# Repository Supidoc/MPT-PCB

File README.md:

# M.P.T.-PCB
The Multipurpose tracker (or just MPT) is a pocket sized device to track you habits. Although it is primarily designed to serve as a habit tracker it can be used for many other things. 

The MPT features a 2.79" 142x428 full color display. To control the device a 4-Way Joystick as well as 5 User Buttons are available.
At the core of the MPT sits an ESP32-S3. The ESP32-S3 has enough power to run the display at 30Hz, features WIFI and Bluetooth LE.
To get accurate timestamps for your habit entries a Microcrystal RTC module is included. The RTC is directly connected to the batteries so that it runs even when the rest of the system is in shutdown.
The whole system is powered by two 10440 570mAH LI-ION batteries by Keepower. The batteries already integrate a protection circuit. MPT features a fuel gauge and a charger to measure battery capacity and charge the device over USB-C. The USB-C Port also serves as the debug interface for ESP's JTAG-Over USB feature.

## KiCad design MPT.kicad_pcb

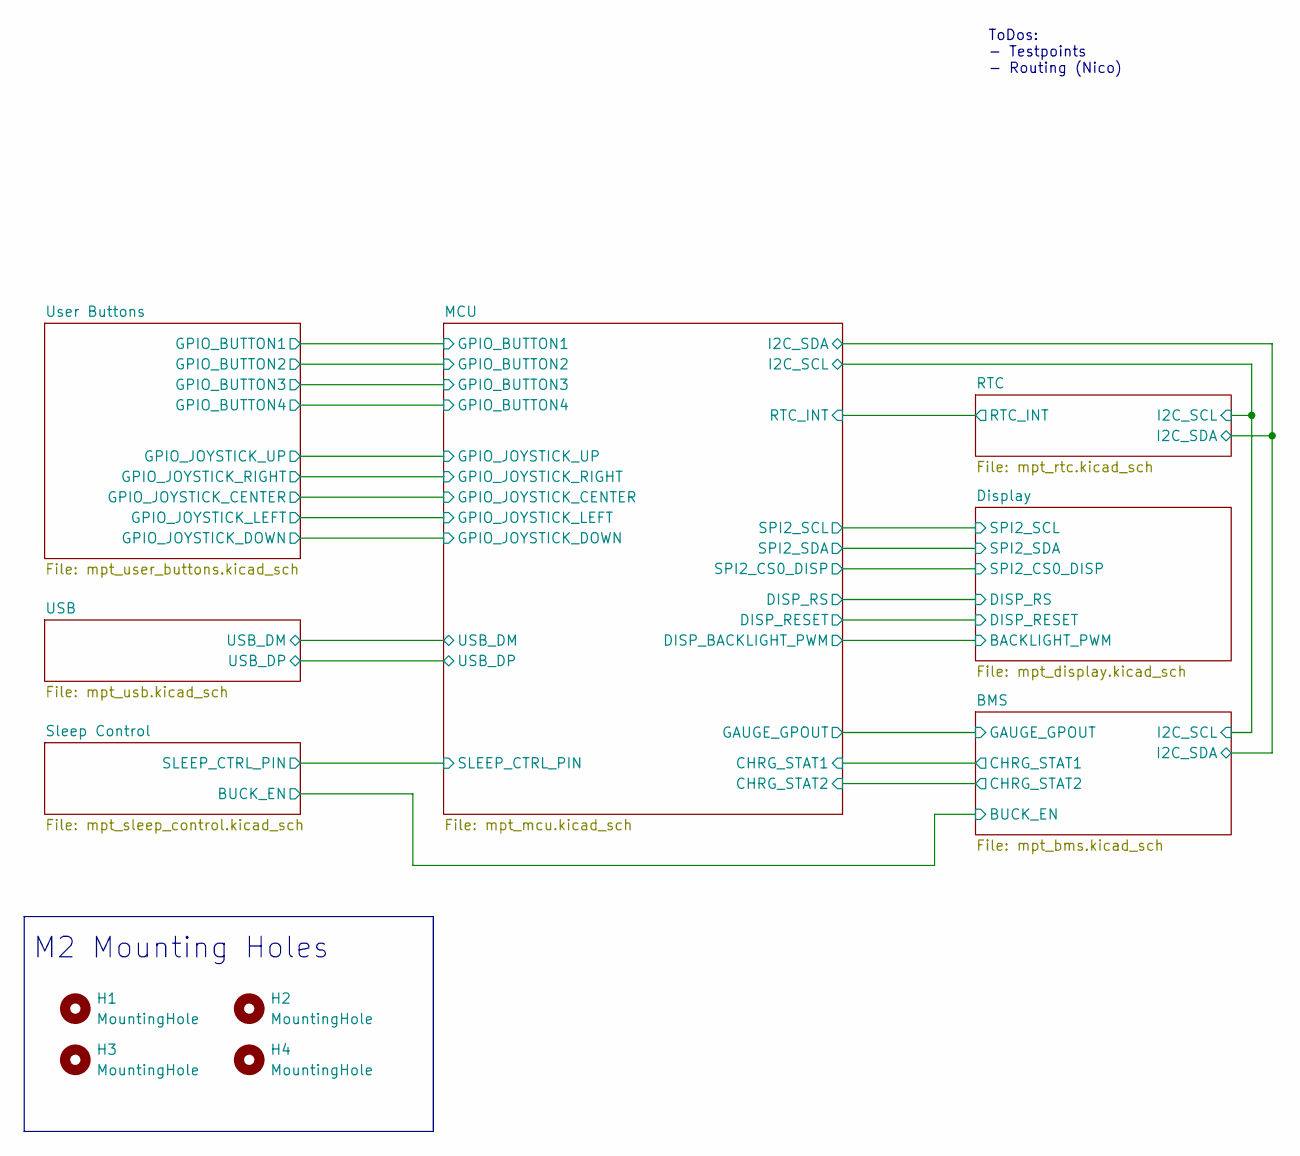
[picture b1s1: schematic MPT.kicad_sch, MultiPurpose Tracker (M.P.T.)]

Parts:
H1, H2, H3, H4: MountingHole; MountingHole_2.2mm_M2

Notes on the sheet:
ToDos: - Testpoints - Routing (Nico)
M2 Mounting Holes

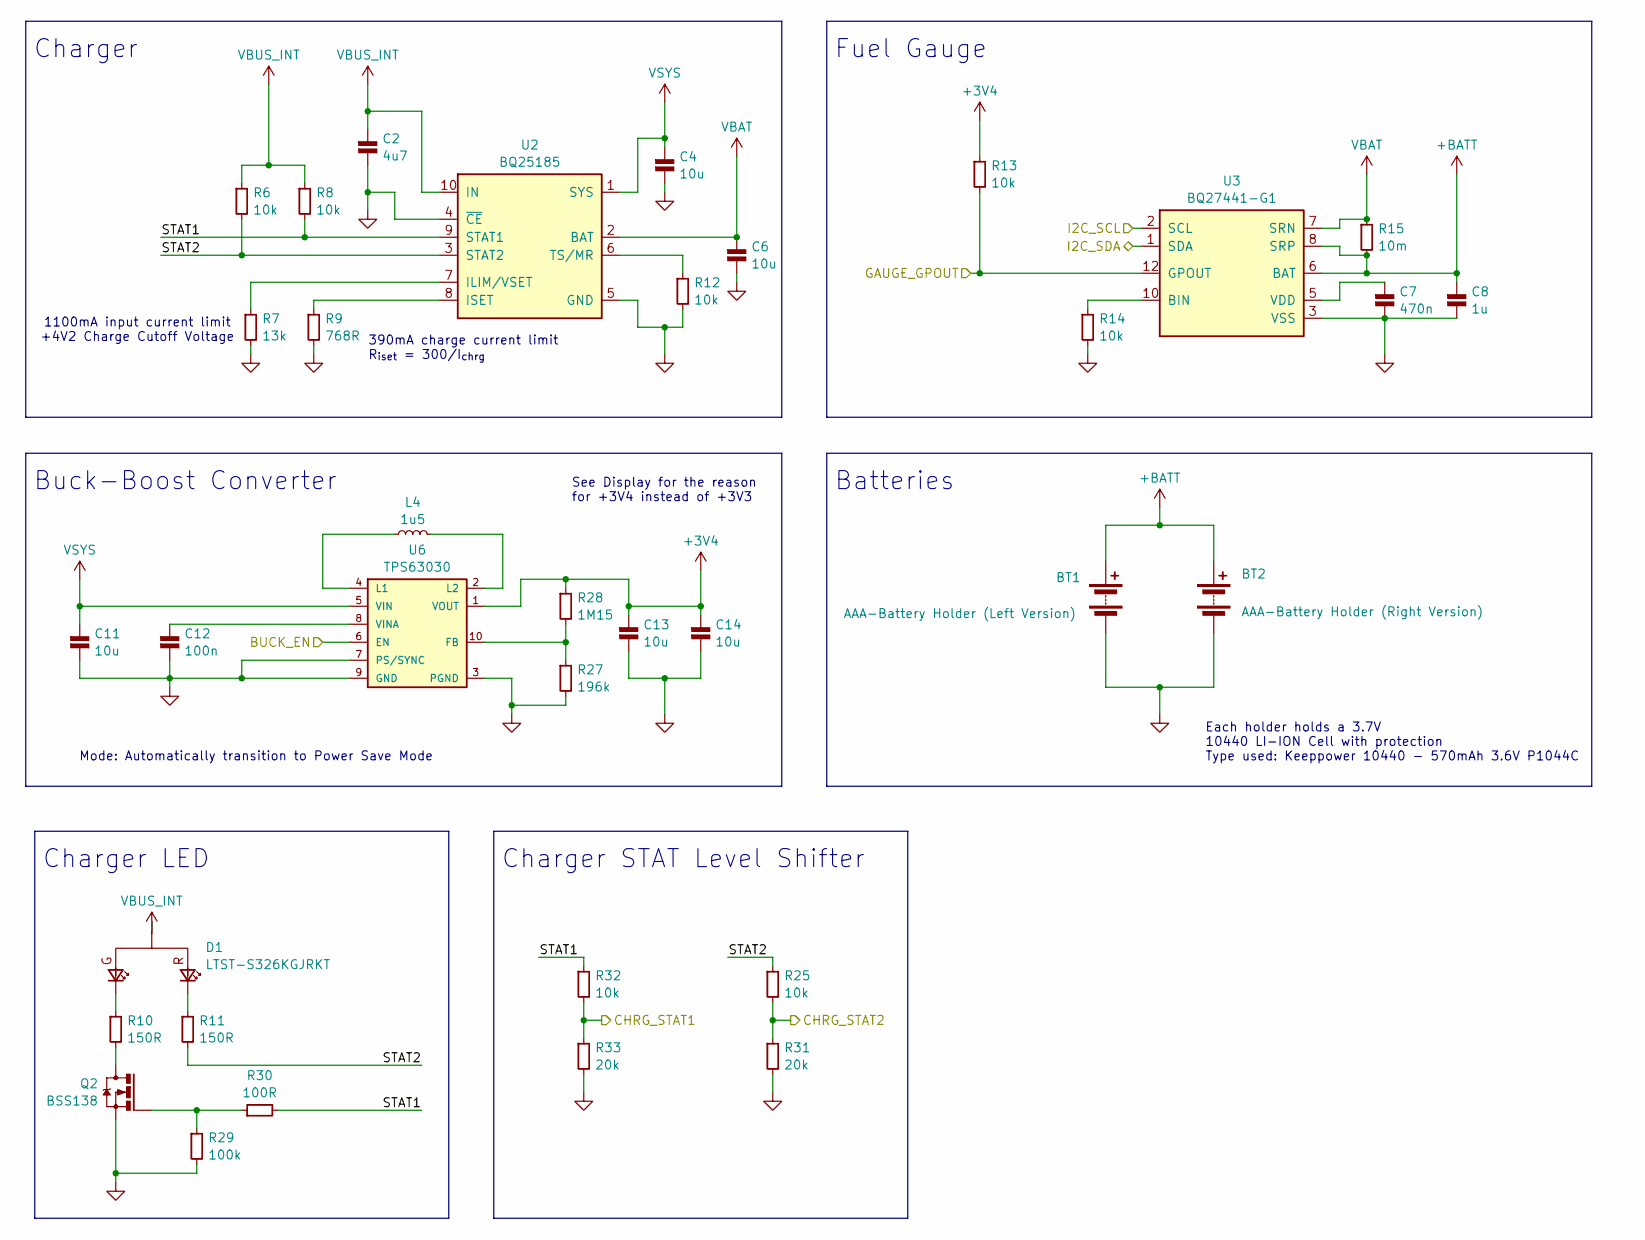
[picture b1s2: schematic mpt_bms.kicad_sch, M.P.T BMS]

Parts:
BT1: AAA-Battery Holder (Left Version); battery_holder_aaa_right_angle_left; MFR# 2466
BT2: AAA-Battery Holder (Right Version); battery_holder_aaa_right_angle_right; MFR# 2466
C2: 4u7; C_0805; Rating 25V 10%; MFR# CC0805KKX7R8BB475
C4, C6, C11, C13, C14: 10u; C_0603; Rating 10V 20%; MFR# CC0603MRX5R6BB106
C7: 470n; C_0603; Rating 16V 10%; MFR# CC0603KRX7R7BB474
C8: 1u; C_0603; Rating 50V 10%; MFR# CC0603KRX7R9BB105
C12: 100n; C_0603; Rating 25V 10%; MFR# CC0603KRX7R8BB104
D1: LTST-S326KGJRKT; LED_RG_0805_Right_Angle; Rating Red 2Vf, Green 2Vf; MFR# LTST-S326KGJRKT
L4: 1u5; L_2.5mmx1.9mm; Rating 2A6, 20%, 80mOhm; MFR# SRP2010TMA-1R5M
Q2: BSS138; SOT-23; Rating 50 V 220mA; MFR# BSS138
R6, R8, R12, R13, R14, R25, R32: 10k; R_0603; Rating 125mW, 1%; MFR# RC0603FR-0710KL
R7: 13k; R_0603; Rating 125mW, 1%; MFR# RC0603FR-0713KL
R9: 768R; R_0603; Rating 125mW, 1%; MFR# RC0603FR-07768RL
R10, R11: 150R; R_0603; Rating 125mW, 1%; MFR# RC0603FR-07150RL
R15: 10m; R_0603; Rating 0.5W, 1%; MFR# PA0603FRE570R01L
R27: 196k; R_0603; Rating 125mW, 1%; MFR# RC0603FR-07196KL
R28: 1M15; R_0603; Rating 125mW, 1%; MFR# RC0603FR-071M15L
R29: 100k; R_0603; Rating 125mW, 1%; MFR# RC0603FR-07100KL
R30: 100R; R_0603; Rating 125mW, 1%; MFR# RC0603FR-07100RL
R31, R33: 20k; R_0603; Rating 125mW, 1%; MFR# RC0603FR-0720KL
U2: BQ25185; WSON-10-1EP_2.2x2mm_P0.4mm; Rating 1 Cell, 1 A; MFR# BQ25185DLHR
U3: BQ27441-G1; VSON-12-1EP_2.5_4mm_P0.4mm; MFR# BQ27441DRZR-G1A
U6: TPS63030; WSON-10-1EP_2.5x2.5mm_P0.5mm; Rating 1A; MFR# TPS63030DSKR

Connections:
+3V4: C13.1, C14.1, R13.1, R28.1, U6.1 (VOUT); also elsewhere on the board
+BATT: BT1.1 (+), BT2.1 (+), C8.1, R15.2, U3.6 (BAT), U3.8 (SRP)
/BMS/BUCK_EN: U6.6 (EN); also elsewhere on the board
/BMS/CHRG_STAT1: R32.2, R33.1; also elsewhere on the board
/BMS/CHRG_STAT2: R25.2, R31.1; also elsewhere on the board
/BMS/GAUGE_GPOUT: R13.2, U3.12 (GPOUT); also elsewhere on the board
/BMS/I2C_SCL: U3.2 (SCL); also elsewhere on the board
/BMS/I2C_SDA: U3.1 (SDA); also elsewhere on the board
/BMS/STAT1: R8.2, R30.2, R32.1, U2.9 (STAT1)
/BMS/STAT2: R6.2, R11.2, R25.1, U2.3 (STAT2)
GND: BT1.2 (-), BT2.2 (-), C2.2, C4.2, C6.2, C7.2, C8.2, C11.2, C12.2, C13.2, C14.2, Q2.2 (S), R7.2, R9.2, R12.2, R14.2, R27.2, R29.2, R31.2, R33.2, U2.0 (PAD), U2.4 (~CE), U2.5 (GND), U3.0 (PAD), U3.3 (VSS), U6.0 (PAD), U6.3 (PGND), U6.7 (PS/SYNC), U6.9 (GND); also elsewhere on the board
unnamed: D1.3 (C_G), R10.1
unnamed: D1.1 (C_R), R11.1
unnamed: Q2.3 (D), R10.2
unnamed: Q2.1 (G), R29.1, R30.1
unnamed: R7.1, U2.7 (ILIM/VSET)
unnamed: R9.1, U2.8 (ISET)
unnamed: R12.1, U2.6 (TS/MR)
unnamed: R14.1, U3.10 (BIN)
unnamed: C7.1, U3.5 (VDD)
unnamed: R27.1, R28.2, U6.10 (FB)
unnamed: L4.1, U6.4 (L1)
unnamed: L4.2, U6.2 (L2)
unnamed: C12.1, U6.8 (VINA)
VBAT: C6.1, R15.1, U2.2 (BAT), U3.7 (SRN); also elsewhere on the board
VBUS_INT: C2.1, D1.2 (A), R6.1, R8.1, U2.10 (IN); also elsewhere on the board
VSYS: C4.1, C11.1, U2.1 (SYS), U6.5 (VIN); also elsewhere on the board

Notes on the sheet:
Charger
Buck-Boost Converter
390mA charge current limit R_{iset} = 300/I_{chrg}
Fuel Gauge
Batteries
Charger STAT Level Shifter
See Display for the reason for +3V4 instead of +3V3
Each holder holds a 3.7V 10440 LI-ION Cell with protection Type used: Keeppower 10440 - 570mAh 3.6V P1044C
Mode: Automatically transition to Power Save Mode
1100mA input current limit +4V2 Charge Cutoff Voltage
Charger LED

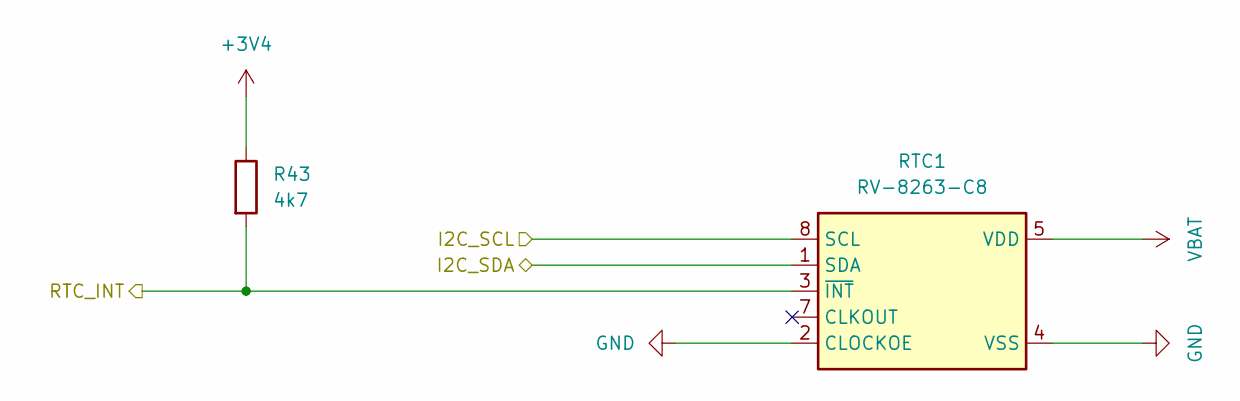
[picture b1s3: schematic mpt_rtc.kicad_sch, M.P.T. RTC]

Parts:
R43: 4k7; R_0603_1608Metric
RTC1: RV-8263-C8; IC_RV-8263-C8-32.768KHZ-20PPM-TA-QC

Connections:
+3V4: R43.1; also elsewhere on the board
/BMS/I2C_SCL: RTC1.8 (SCL); also elsewhere on the board
/BMS/I2C_SDA: RTC1.1 (SDA); also elsewhere on the board
/MCU/RTC_INT: R43.2, RTC1.3 (~INT); also elsewhere on the board
GND: RTC1.2 (CLOCKOE), RTC1.4 (VSS); also elsewhere on the board
VBAT: RTC1.5 (VDD); also elsewhere on the board

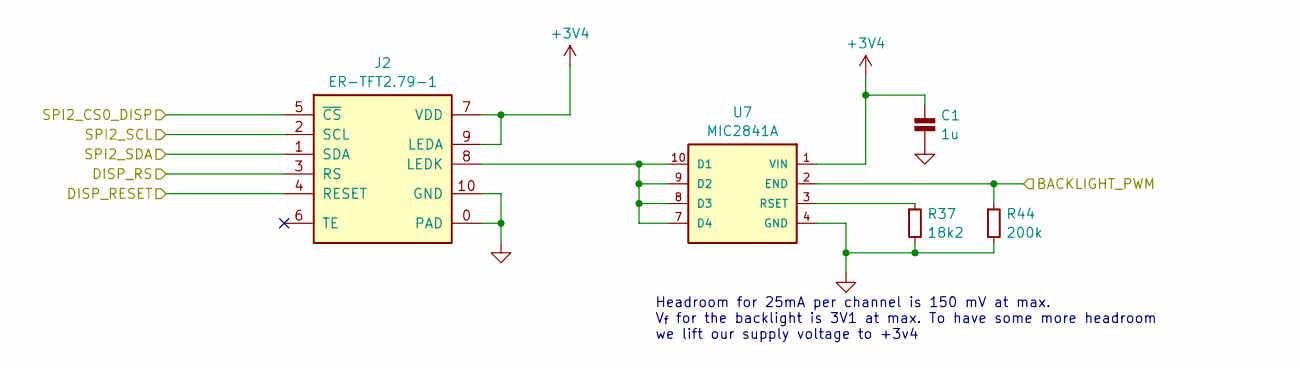
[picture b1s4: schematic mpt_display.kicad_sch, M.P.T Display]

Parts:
C1: 1u; C_0603; Rating 50V 10%; MFR# CC0603KRX7R9BB105
J2: ER-TFT2.79-1; Rating 2.79" IPS TFT LCD; MFR# ER-TFT2.79-1
R37: 18k2; R_0603; Rating 125mW, 1%; MFR# RC0603FR-0718K2L
R44: 200k; R_0603; Rating 125mW, 1%; MFR# RC0603FR-07200KL
U7: MIC2841A; MLF-10_MT_MCH; Rating 20mA 4 Ch; MFR# MIC2841AYMT-TR

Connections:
+3V4: C1.1, J2.7 (VDD), J2.9 (LEDA), U7.1 (VIN); also elsewhere on the board
/Display/BACKLIGHT_PWM: R44.1, U7.2 (END); also elsewhere on the board
/Display/DISP_RESET: J2.4 (RESET); also elsewhere on the board
/Display/DISP_RS: J2.3 (RS); also elsewhere on the board
/Display/SPI2_CS0_DISP: J2.5 (~CS); also elsewhere on the board
/Display/SPI2_SCL: J2.2 (SCL); also elsewhere on the board
/Display/SPI2_SDA: J2.1 (SDA); also elsewhere on the board
GND: C1.2, J2.0 (PAD), J2.10 (GND), R37.2, R44.2, U7.0 (PAD), U7.4 (GND); also elsewhere on the board
unnamed: J2.8 (LEDK), U7.7 (D4), U7.8 (D3), U7.9 (D2), U7.10 (D1)
unnamed: R37.1, U7.3 (RSET)

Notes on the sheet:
Headroom for 25mA per channel is 150 mV at max. V_{f} for the backlight is 3V1 at max. To have some more headroom we lift our supply voltage to +3v4

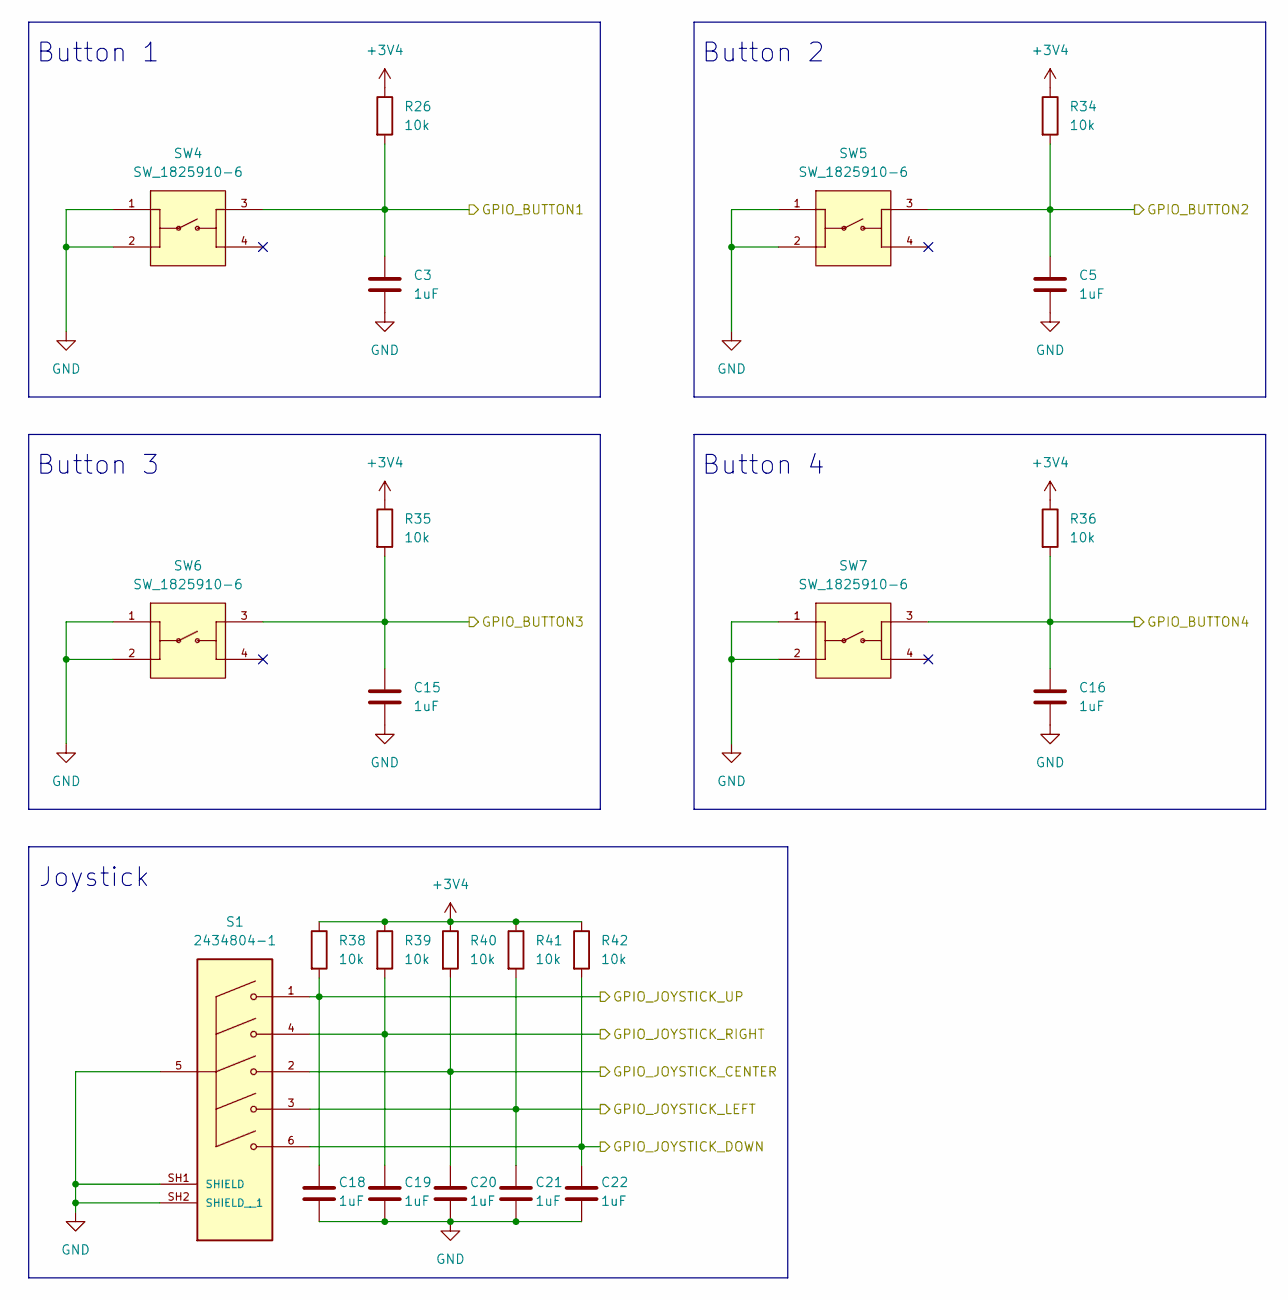
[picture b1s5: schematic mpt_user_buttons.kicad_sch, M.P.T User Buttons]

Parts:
C3, C5, C15, C16, C18, C19, C20, C21, C22: 1uF; C_0603_1608Metric
R26, R34, R35, R36, R38, R39, R40, R41, R42: 10k; R_0603_1608Metric
S1: 2434804-1; SW_2434804-1; PARTREV A
SW4, SW5, SW6, SW7: SW_1825910-6; SW_1825910-6-4; PARTREV C10

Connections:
+3V4: R26.1, R34.1, R35.1, R36.1, R38.1, R39.1, R40.1, R41.1, R42.1; also elsewhere on the board
/MCU/GPIO_BUTTON1: C3.1, R26.2, SW4.3; also elsewhere on the board
/MCU/GPIO_BUTTON2: C5.1, R34.2, SW5.3; also elsewhere on the board
/MCU/GPIO_BUTTON3: C15.1, R35.2, SW6.3; also elsewhere on the board
/MCU/GPIO_BUTTON4: C16.1, R36.2, SW7.3; also elsewhere on the board
/MCU/GPIO_JOYSTICK_CENTER: C20.1, R40.2, S1.2; also elsewhere on the board
/MCU/GPIO_JOYSTICK_DOWN: C22.1, R42.2, S1.6; also elsewhere on the board
/MCU/GPIO_JOYSTICK_LEFT: C21.1, R41.2, S1.3; also elsewhere on the board
/MCU/GPIO_JOYSTICK_RIGHT: C19.1, R39.2, S1.4; also elsewhere on the board
/MCU/GPIO_JOYSTICK_UP: C18.1, R38.2, S1.1; also elsewhere on the board
GND: C3.2, C5.2, C15.2, C16.2, C18.2, C19.2, C20.2, C21.2, C22.2, S1.5, S1.SH1 (SHIELD), S1.SH2 (SHIELD__1), SW4.1, SW4.2, SW5.1, SW5.2, SW6.1, SW6.2, SW7.1, SW7.2; also elsewhere on the board

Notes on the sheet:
Button 2
Button 4
Joystick
Button 1
Button 3

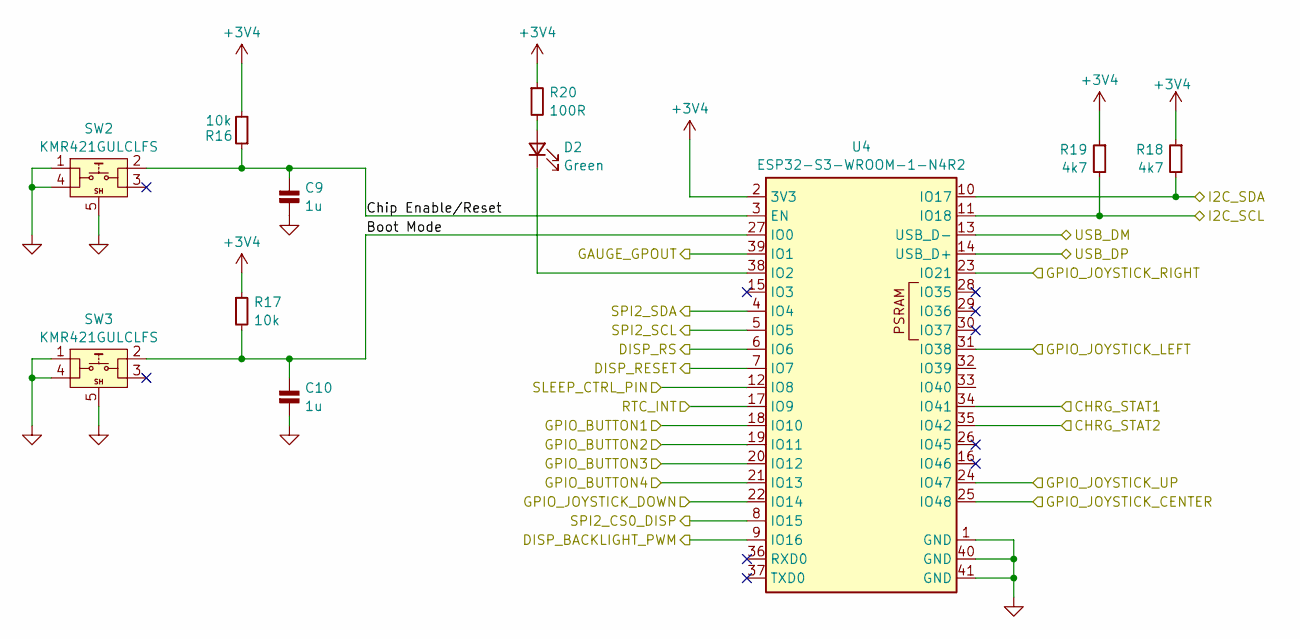
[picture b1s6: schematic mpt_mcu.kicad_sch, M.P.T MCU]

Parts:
C9, C10: 1u; C_0603; Rating 50V 10%; MFR# CC0603KRX7R9BB105
D2: Green; D_0603; Rating 2v1 20mA 569nm; MFR# LTST-C190GKT
R16, R17: 10k; R_0603; Rating 125mW, 1%; MFR# RC0603FR-0710KL
R18, R19: 4k7; R_0603; Rating 100mW, 1%; MFR# RC0603FR-074K7L
R20: 100R; R_0603; Rating 125mW, 1%; MFR# RC0603FR-07100RL
SW2, SW3: KMR421GULCLFS; Rating 1VA; MFR# KMR421GULCLFS
U4: ESP32-S3-WROOM-1-N4R2; ESP32_S3_WROOM_1; Rating 4 MB Flash, 2 MB PSRAM; MFR# ESP32-S3-WROOM-1-N4R2

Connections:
+3V4: R16.2, R17.1, R18.1, R19.1, R20.1, U4.2 (3V3); also elsewhere on the board
/BMS/CHRG_STAT1: U4.34 (IO41); also elsewhere on the board
/BMS/CHRG_STAT2: U4.35 (IO42); also elsewhere on the board
/BMS/GAUGE_GPOUT: U4.39 (IO1); also elsewhere on the board
/BMS/I2C_SCL: R19.2, U4.11 (IO18); also elsewhere on the board
/BMS/I2C_SDA: R18.2, U4.10 (IO17); also elsewhere on the board
/Display/BACKLIGHT_PWM: U4.9 (IO16); also elsewhere on the board
/Display/DISP_RESET: U4.7 (IO7); also elsewhere on the board
/Display/DISP_RS: U4.6 (IO6); also elsewhere on the board
/Display/SPI2_CS0_DISP: U4.8 (IO15); also elsewhere on the board
/Display/SPI2_SCL: U4.5 (IO5); also elsewhere on the board
/Display/SPI2_SDA: U4.4 (IO4); also elsewhere on the board
/MCU/Boot Mode: C10.1, R17.2, SW3.2, U4.27 (IO0)
/MCU/Chip Enable/Reset: C9.1, R16.1, SW2.2, U4.3 (EN)
/MCU/GPIO_BUTTON1: U4.18 (IO10); also elsewhere on the board
/MCU/GPIO_BUTTON2: U4.19 (IO11); also elsewhere on the board
/MCU/GPIO_BUTTON3: U4.20 (IO12); also elsewhere on the board
/MCU/GPIO_BUTTON4: U4.21 (IO13); also elsewhere on the board
/MCU/GPIO_JOYSTICK_CENTER: U4.25 (IO48); also elsewhere on the board
/MCU/GPIO_JOYSTICK_DOWN: U4.22 (IO14); also elsewhere on the board
/MCU/GPIO_JOYSTICK_LEFT: U4.31 (IO38); also elsewhere on the board
/MCU/GPIO_JOYSTICK_RIGHT: U4.23 (IO21); also elsewhere on the board
/MCU/GPIO_JOYSTICK_UP: U4.24 (IO47); also elsewhere on the board
/MCU/RTC_INT: U4.17 (IO9); also elsewhere on the board
/MCU/SLEEP_CTRL_PIN: U4.12 (IO8); also elsewhere on the board
/MCU/USB_DM: U4.13 (USB_D-); also elsewhere on the board
/MCU/USB_DP: U4.14 (USB_D+); also elsewhere on the board
GND: C9.2, C10.2, SW2.1, SW2.4 (3), SW2.5 (SH), SW3.1, SW3.4 (3), SW3.5 (SH), U4.1 (GND), U4.40 (GND), U4.41 (GND); also elsewhere on the board
unnamed: D2.1 (A), R20.2
unnamed: D2.2 (K), U4.38 (IO2)

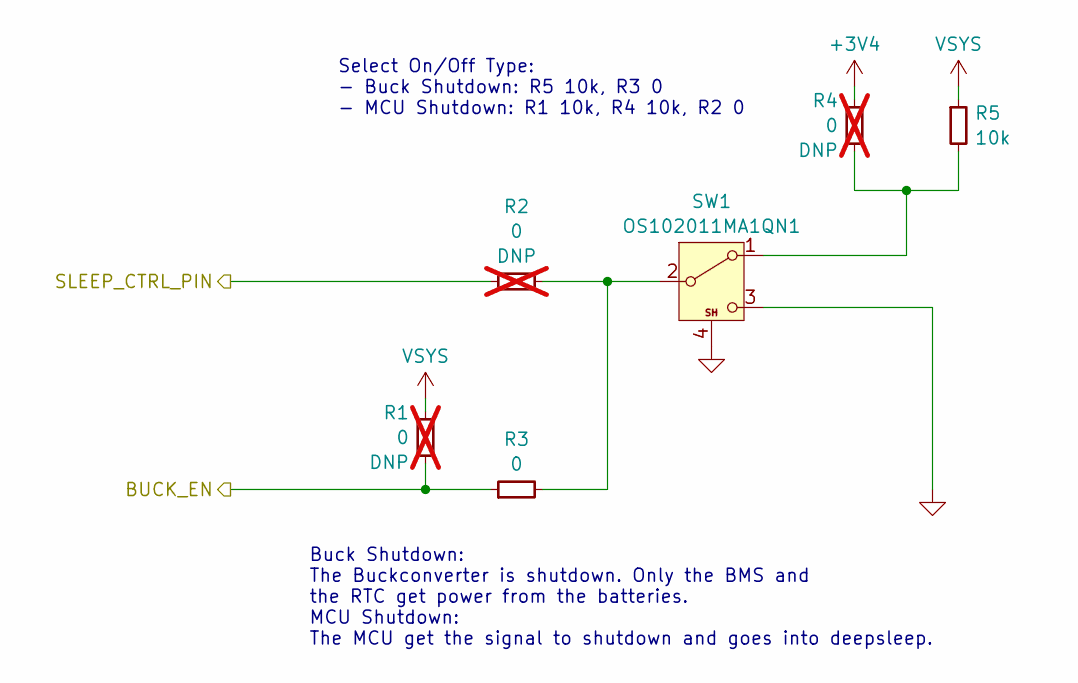
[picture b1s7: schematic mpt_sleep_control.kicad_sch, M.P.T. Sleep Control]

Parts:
R1, R2, R4: 0; R_0603_DNP; not fitted
R3: 0; R_0603; Rating 100mW; MFR# RC0603JR-070RL
R5: 10k; R_0603; Rating 125mW, 1%; MFR# RC0603FR-0710KL
SW1: OS102011MA1QN1; OS102011MA1QN1_CNK; Rating 100MA 12V Non-shorting; MFR# OS102011MA1QN1

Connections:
+3V4: R4.1; also elsewhere on the board
/BMS/BUCK_EN: R1.2, R3.1; also elsewhere on the board
/MCU/SLEEP_CTRL_PIN: R2.1; also elsewhere on the board
GND: SW1.3 (C), SW1.4 (SH); also elsewhere on the board
unnamed: R4.2, R5.2, SW1.1 (A)
unnamed: R2.2, R3.2, SW1.2 (B)
VSYS: R1.1, R5.1; also elsewhere on the board

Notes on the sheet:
Buck Shutdown: The Buckconverter is shutdown. Only the BMS and the RTC get power from the batteries. MCU Shutdown: The MCU get the signal to shutdown and goes into deepsleep.
Select On/Off Type: - Buck Shutdown: R5 10k, R3 0 - MCU Shutdown: R1 10k, R4 10k, R2 0

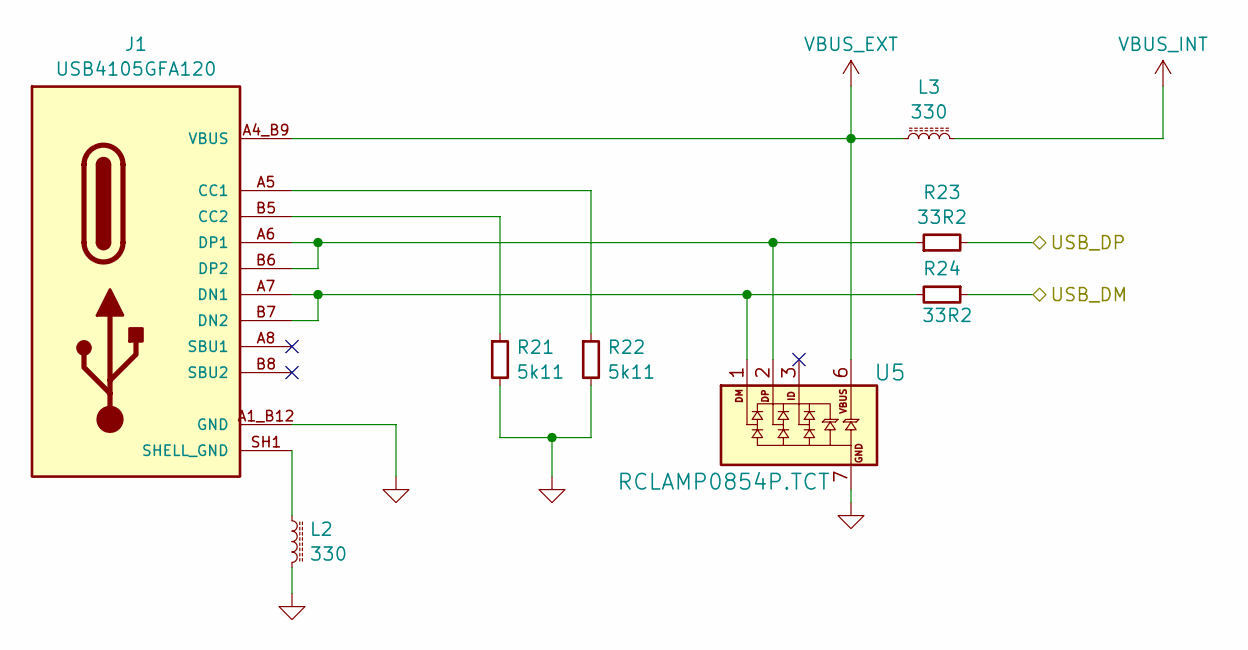
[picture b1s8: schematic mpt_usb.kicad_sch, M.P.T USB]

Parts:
J1: USB4105GFA120; GCT_USB4105GFA120; Rating 16 Pin; MFR# USB4105-GF-A-120
L2, L3: 330; L_0603; Rating 330 Ohms @ 100 MHz 1.7A 80mOhm; MFR# MPZ1608S331ATA00
R21, R22: 5k11; R_0603; Rating 125mW, 1%; MFR# RC0603FR-075K11L
R23, R24: 33R2; R_0603; Rating 125mW, 1%; MFR# RC0603FR-0733R2L
U5: RCLAMP0854P.TCT; UFDFN06_1P6X1P6; Rating 5.5VWM 30VC; MFR# RCLAMP0854P.TCT

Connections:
/MCU/USB_DM: R24.1; also elsewhere on the board
/MCU/USB_DP: R23.2; also elsewhere on the board
GND: J1.A1_B12 (GND), J1.B1_A12 (GND), L2.2, R21.2, R22.2, U5.7 (GND); also elsewhere on the board
unnamed: J1.A5 (CC1), R22.1
unnamed: J1.B5 (CC2), R21.1
unnamed: J1.A7 (DN1), J1.B7 (DN2), R24.2, U5.1 (DM)
unnamed: J1.A6 (DP1), J1.B6 (DP2), R23.1, U5.2 (DP)
SHELL_GND: J1.SH1 (SHELL_GND), J1.SH2 (SHELL_GND), J1.SH3 (SHELL_GND), J1.SH4 (SHELL_GND), L2.1
VBUS_EXT: J1.A4_B9 (VBUS), J1.B4_A9 (VBUS), L3.1, U5.6 (VBUS)
VBUS_INT: L3.2; also elsewhere on the board

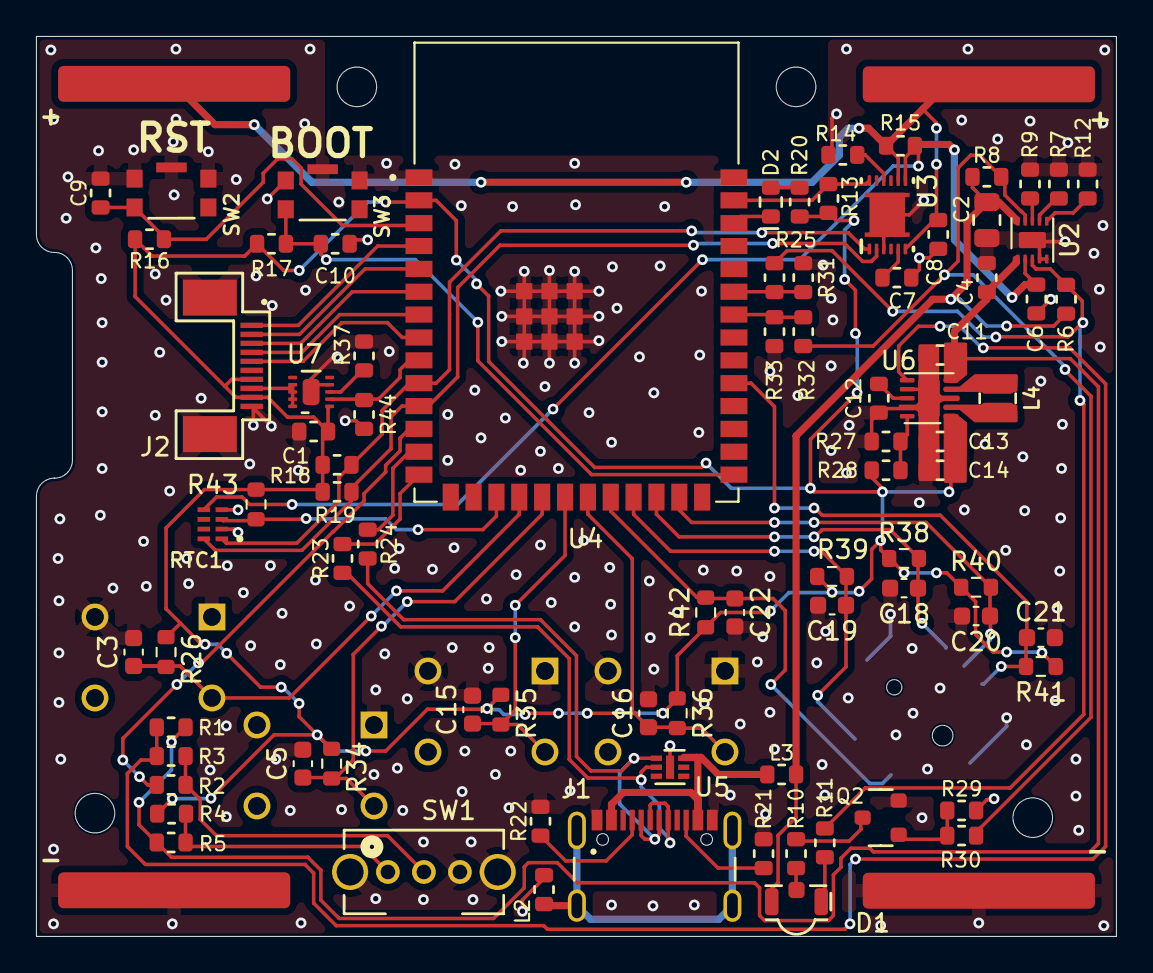
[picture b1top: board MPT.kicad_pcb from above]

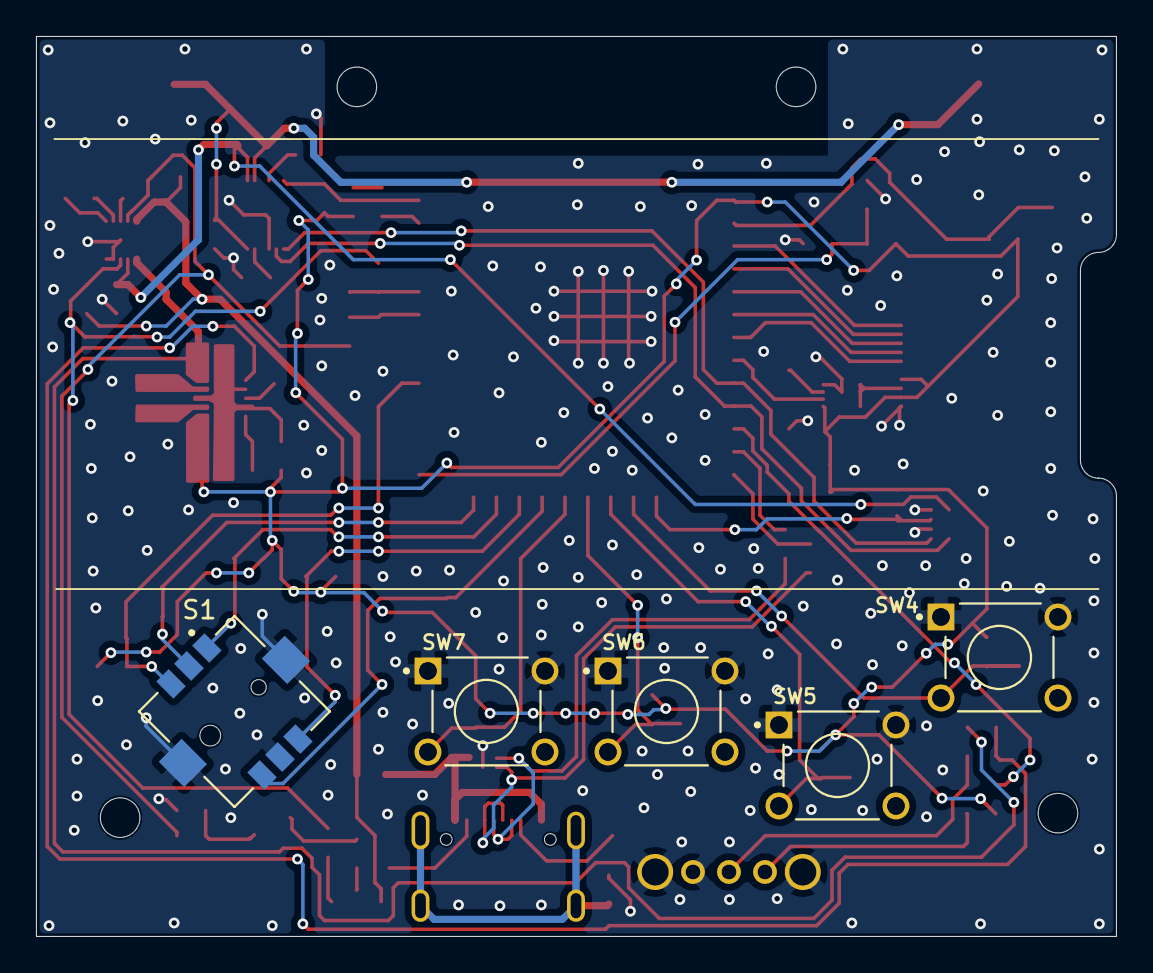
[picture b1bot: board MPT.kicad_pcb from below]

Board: 2 copper layers, 60.0 x 50.0 mm, 94 parts (5 on the bottom side), 60 nets.
